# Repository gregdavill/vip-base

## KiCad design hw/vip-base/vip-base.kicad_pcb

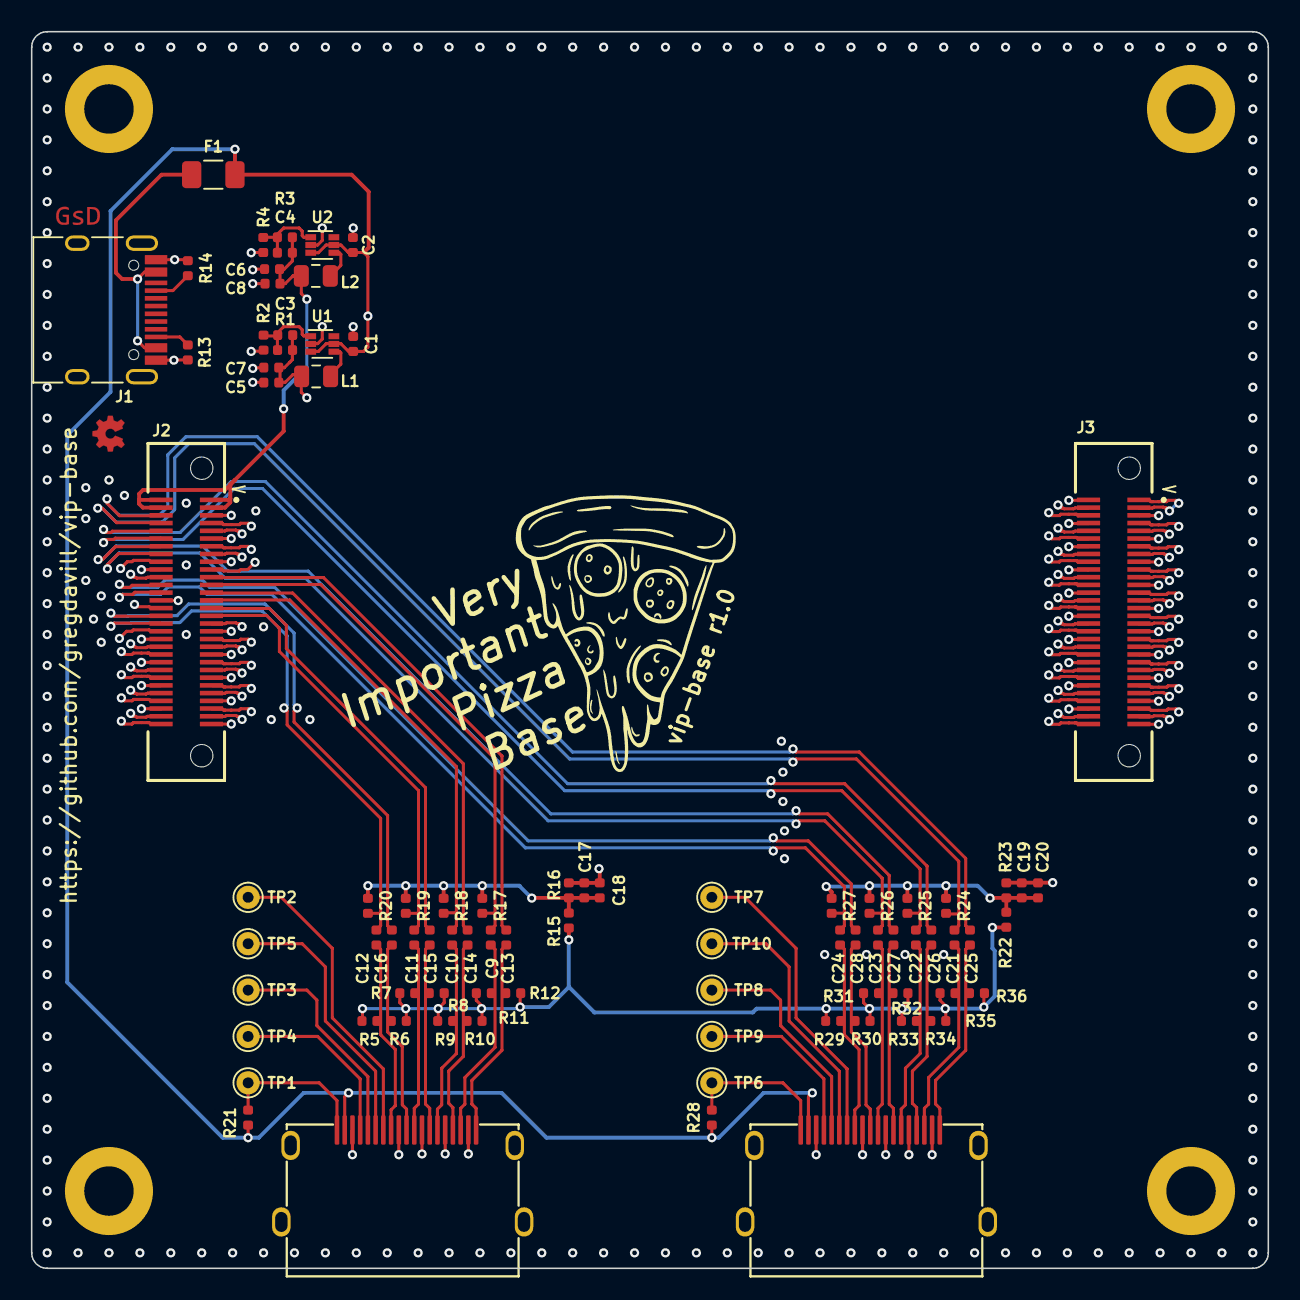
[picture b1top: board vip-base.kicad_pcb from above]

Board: 4 copper layers, 80.0 x 80.0 mm, 88 parts (0 on the bottom side), 56 nets.

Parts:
C1, C2, C5, C6, C7, C8: 10uF; C_0402_1005Metric
C3, C4: 10pF; C_0402_1005Metric
C9, C10, C11, C12, C13, C14, C15, C16, C17, C19, C21, C22, C23, C24, C25, C26, C27, C28: 0.1u; C_0402_1005Metric
C18, C20: 4.7u; C_0402_1005Metric
F1: Polyfuse_Small; L_1206_3216Metric
H1, H2, H3, H4: MountingHole_3.2mm_M3_ISO7380_Pad
J1: USB_C_Receptacle_USB2.0; USB_C_Receptacle_HRO_TYPE-C-31-M-12
J2, J3: Conn_02x30_Odd_Even; SAMTEC_ERM5-030-05.0-L-DV-K-TR
J4, J5: HDMI_A_1.4; HDMI-10029449-111RLF
L1, L2: 2.2uH; L_0805_2012Metric
R1, R3: 360k; R_0402_1005Metric
R2, R4: 82k; R_0402_1005Metric
R5, R6, R7, R8, R9, R10, R11, R12, R29, R30, R31, R32, R33, R34, R35, R36: 50R; R_0402_1005Metric
R13, R14: 5.1k; R_0402_1005Metric
R15, R22: 2k; R_0402_1005Metric
R16, R21, R23, R28: 1k; R_0402_1005Metric
R17, R18, R19, R20, R24, R25, R26, R27: 47k; R_0402_1005Metric
TP1, TP2, TP3, TP4, TP5, TP6, TP7, TP8, TP9, TP10: TestPoint; TestPoint_THTPad_D1.5mm_Drill0.7mm
U1, U2: TLV62569DRL; SOT-563

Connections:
+3V3: R5.1, R6.1, R7.1, R8.1, R9.1, R10.1, R11.1, R12.1, R15.1, R22.1, R29.1, R30.1, R31.1, R32.1, R33.1, R34.1, R35.1, R36.1
+5V: C1.2, C2.2, F1.2, J3.2, J3.4, J3.6, J4.18 (+5V), J5.18 (+5V), R21.1, R28.1, U1.3 (VIN), U1.5 (EN), U2.3 (VIN), U2.5 (EN)
/HDMI0.CK_N: C12.1, J2.34, R20.2
/HDMI0.CK_P: C16.1, J2.32
/HDMI0.D0_N: C11.1, J2.31, R19.2
/HDMI0.D0_P: C15.1, J2.29
/HDMI0.D1_N: C10.1, J2.27, R18.2
/HDMI0.D1_P: C14.1, J2.25
/HDMI0.D2_N: C9.1, J2.23, R17.2
/HDMI0.D2_P: C13.1, J2.21
/HDMI1.CK_N: C24.1, J2.26, R27.2
/HDMI1.CK_P: C28.1, J2.24
/HDMI1.D0_N: C23.1, J2.16, R26.2
/HDMI1.D0_P: C27.1, J2.14
/HDMI1.D1_N: C22.1, J2.12, R25.2
/HDMI1.D1_P: C26.1, J2.10
/HDMI1.D2_N: C21.1, J2.8, R24.2
/HDMI1.D2_P: C25.1, J2.6
/hdmi-0/_CK_N: C12.2, J4.12 (CK-), R5.2
/hdmi-0/_CK_P: C16.2, J4.10 (CK+), R6.2
/hdmi-0/_D0_N: C11.2, J4.9 (D0-), R7.2
/hdmi-0/_D0_P: C15.2, J4.7 (D0+), R8.2
/hdmi-0/_D1_N: C10.2, J4.6 (D1-), R9.2
/hdmi-0/_D1_P: C14.2, J4.4 (D1+), R10.2
/hdmi-0/_D2_N: C9.2, J4.3 (D2-), R11.2
/hdmi-0/_D2_P: C13.2, J4.1 (D2+), R12.2
/hdmi-01/_CK_N: C24.2, J5.12 (CK-), R29.2
/hdmi-01/_CK_P: C28.2, J5.10 (CK+), R30.2
/hdmi-01/_D0_N: C23.2, J5.9 (D0-), R31.2
/hdmi-01/_D0_P: C27.2, J5.7 (D0+), R32.2
/hdmi-01/_D1_N: C22.2, J5.6 (D1-), R33.2
/hdmi-01/_D1_P: C26.2, J5.4 (D1+), R34.2
/hdmi-01/_D2_N: C21.2, J5.3 (D2-), R35.2
/hdmi-01/_D2_P: C25.2, J5.1 (D2+), R36.2
GND: C1.1, C2.1, C5.1, C6.1, C7.1, C8.1, C17.2, C18.2, C19.2, C20.2, J1.A1 (GND), J1.A12 (GND), J1.B1 (GND), J1.B12 (GND), J1.S1 (SHIELD), J2.17, J2.18, J2.19, J2.20, J2.22, J2.33, J2.35, J2.36, J2.38, J2.40, J2.53, J2.54, J2.55, J2.56, J3.5, J3.8, J3.11, J3.14, J3.17, J3.20, J3.26, J3.34, J3.40, J3.46, J3.52, J3.55, J3.57, J3.58, J3.59, J4.2 (D2S), J4.5 (D1S), J4.8 (D0S), J4.11 (CKS), J4.17 (GND), J4.SH, J5.2 (D2S), J5.5 (D1S), J5.8 (D0S), J5.11 (CKS), J5.17 (GND), J5.SH, R2.2, R4.2, R13.1, R14.1, R16.2, R23.2, U1.2 (GND), U2.2 (GND)
unnamed: C3.1, R1.1, R2.1, U1.1 (FB)
unnamed: C4.1, R3.1, R4.1, U2.1 (FB)
unnamed: C17.1, C18.1, R15.2, R16.1, R17.1, R18.1, R19.1, R20.1
unnamed: C19.1, C20.1, R22.2, R23.1, R24.1, R25.1, R26.1, R27.1
unnamed: F1.1, J1.A4 (VBUS), J1.A9 (VBUS), J1.B4 (VBUS), J1.B9 (VBUS)
unnamed: J1.A5 (CC1), R14.2
unnamed: J1.B5 (CC2), R13.2
unnamed: J4.13 (CEC), TP2.1
unnamed: J4.14 (UTILITY/HEAC+), TP5.1
unnamed: J4.15 (SCL), TP3.1
unnamed: J4.16 (SDA), TP4.1
unnamed: J4.19 (HPD/HEAC-), R21.2, TP1.1
unnamed: J5.13 (CEC), TP7.1
unnamed: J5.14 (UTILITY/HEAC+), TP10.1
unnamed: J5.15 (SCL), TP8.1
unnamed: J5.16 (SDA), TP9.1
unnamed: J5.19 (HPD/HEAC-), R28.2, TP6.1
unnamed: L1.1, U1.4 (SW)
unnamed: L2.1, U2.4 (SW)
P2.5V: C3.2, C5.2, C7.2, J2.57, J2.58, J2.59, J2.60, J3.22, J3.24, L1.2, R1.2
P3.3V: C4.2, C6.2, C8.2, J2.1, J2.2, J2.3, J2.4, J3.1, J3.3, L2.2, R3.2

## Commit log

2020-10-21 WIP: Initial commit of KiCad project
2020-10-31 hw: Finish main routing
2020-10-31 hw: Add gerbers
